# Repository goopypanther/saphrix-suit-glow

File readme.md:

#Daisy-chainable RGB LED boards, interfaced through clocked serial (shift register).#

Daisy chain slave, single address:

Daisy chain slave, dual address:

ISM 400mhz remote control:

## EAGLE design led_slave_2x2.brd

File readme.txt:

Daisy-chainable RGB LED boards, interfaced through clocked serial (shift register).

Daisy chain slave, single address:
(https://github.com/JeremyRuhland/saphrix-suit-glow/raw/master/led_slave_1x2.png)

Daisy chain slave, dual address:
(https://github.com/JeremyRuhland/saphrix-suit-glow/raw/master/led_slave_2x2.png)

ISM 400mhz remote control:
(https://raw.github.com/JeremyRuhland/saphrix-suit-glow/master/led_remote.png)

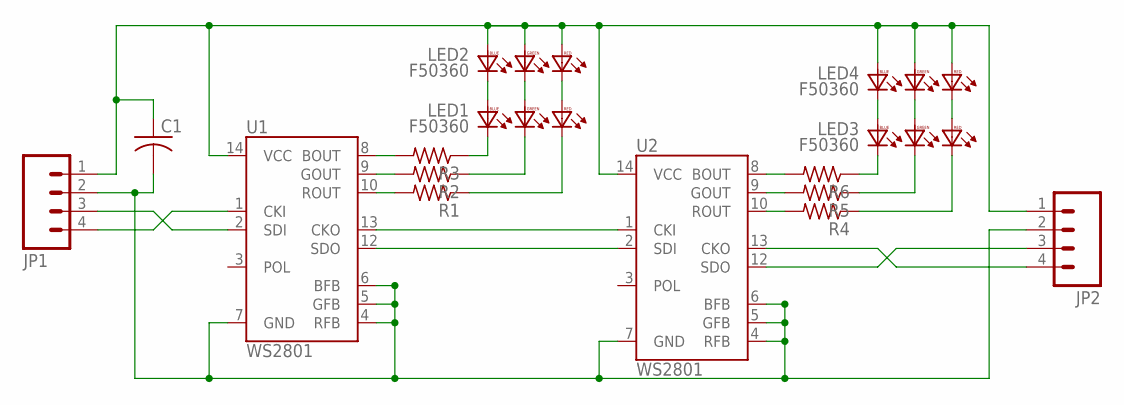
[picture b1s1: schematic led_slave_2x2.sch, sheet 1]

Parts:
C1: C-USC1206; C1206
JP1, JP2: M04LONGPADS; 1X04_LONGPADS
LED1, LED2, LED3, LED4: F50360
R1, R2, R3, R4, R5, R6: R-US_R1206; R1206
U1, U2: WS2801; SOP-14

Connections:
unnamed: JP1.3, U1.2 (SDI)
unnamed: JP1.4, U1.1 (CKI)
unnamed: U1.13 (CKO), U2.1 (CKI)
unnamed: U1.12 (SDO), U2.2 (SDI)
unnamed: R1.2, U1.10 (ROUT)
unnamed: R2.2, U1.9 (GOUT)
unnamed: R3.2, U1.8 (BOUT)
unnamed: LED3.BA, LED4.BC
unnamed: LED3.GA, LED4.GC
unnamed: LED3.RA, LED4.RC
unnamed: LED1.BC, R3.1
unnamed: LED1.GC, R2.1
unnamed: JP2.3, U2.12 (SDO)
unnamed: JP2.4, U2.13 (CKO)
unnamed: LED1.BA, LED2.BC
unnamed: LED1.GA, LED2.GC
unnamed: LED1.RA, LED2.RC
unnamed: LED3.BC, R6.1
unnamed: LED3.GC, R5.1
unnamed: LED3.RC, R4.1
unnamed: LED1.RC, R1.1
unnamed: R6.2, U2.8 (BOUT)
unnamed: R5.2, U2.9 (GOUT)
unnamed: R4.2, U2.10 (ROUT)
unnamed: C1.2, JP1.2, JP2.2, U1.4 (RFB), U1.5 (GFB), U1.6 (BFB), U1.7 (GND), U2.4 (RFB), U2.5 (GFB), U2.6 (BFB), U2.7 (GND)
unnamed: C1.1, JP1.1, JP2.1, LED2.BA, LED2.GA, LED2.RA, LED4.BA, LED4.GA, LED4.RA, U1.14 (VCC), U2.14 (VCC)

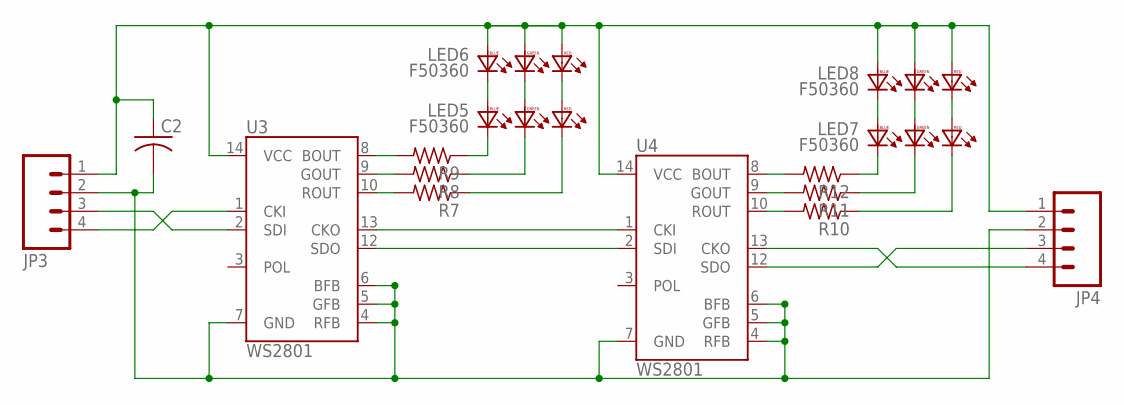
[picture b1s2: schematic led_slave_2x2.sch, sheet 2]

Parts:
C2: C-USC1206; C1206
JP3, JP4: M04LONGPADS; 1X04_LONGPADS
LED5, LED6, LED7, LED8: F50360
R7, R8, R9, R10, R11, R12: R-US_R1206; R1206
U3, U4: WS2801; SOP-14

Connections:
unnamed: U3.13 (CKO), U4.1 (CKI)
unnamed: U3.12 (SDO), U4.2 (SDI)
unnamed: LED5.BA, LED6.BC
unnamed: LED5.GA, LED6.GC
unnamed: LED5.RA, LED6.RC
unnamed: R7.2, U3.10 (ROUT)
unnamed: R8.2, U3.9 (GOUT)
unnamed: R9.2, U3.8 (BOUT)
unnamed: LED5.BC, R9.1
unnamed: LED5.GC, R8.1
unnamed: LED5.RC, R7.1
unnamed: LED7.BA, LED8.BC
unnamed: LED7.GA, LED8.GC
unnamed: LED7.RA, LED8.RC
unnamed: LED7.BC, R12.1
unnamed: LED7.GC, R11.1
unnamed: LED7.RC, R10.1
unnamed: R12.2, U4.8 (BOUT)
unnamed: R11.2, U4.9 (GOUT)
unnamed: R10.2, U4.10 (ROUT)
unnamed: C2.2, JP3.2, JP4.2, U3.4 (RFB), U3.5 (GFB), U3.6 (BFB), U3.7 (GND), U4.4 (RFB), U4.5 (GFB), U4.6 (BFB), U4.7 (GND)
unnamed: JP3.3, U3.2 (SDI)
unnamed: JP3.4, U3.1 (CKI)
unnamed: JP4.3, U4.12 (SDO)
unnamed: JP4.4, U4.13 (CKO)
unnamed: C2.1, JP3.1, JP4.1, LED6.BA, LED6.GA, LED6.RA, LED8.BA, LED8.GA, LED8.RA, U3.14 (VCC), U4.14 (VCC)

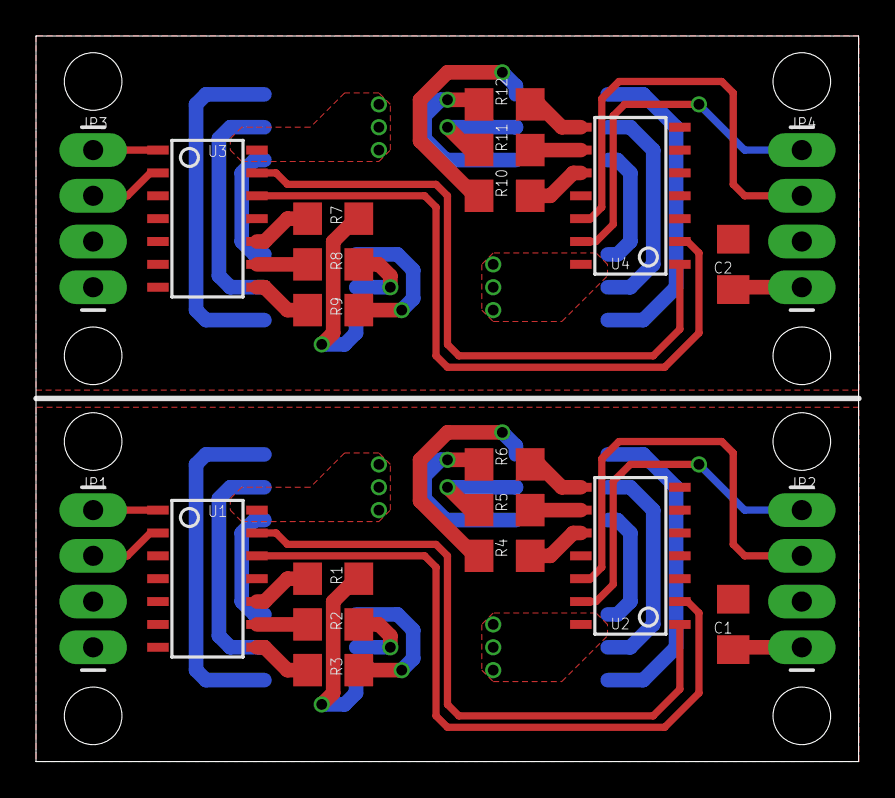
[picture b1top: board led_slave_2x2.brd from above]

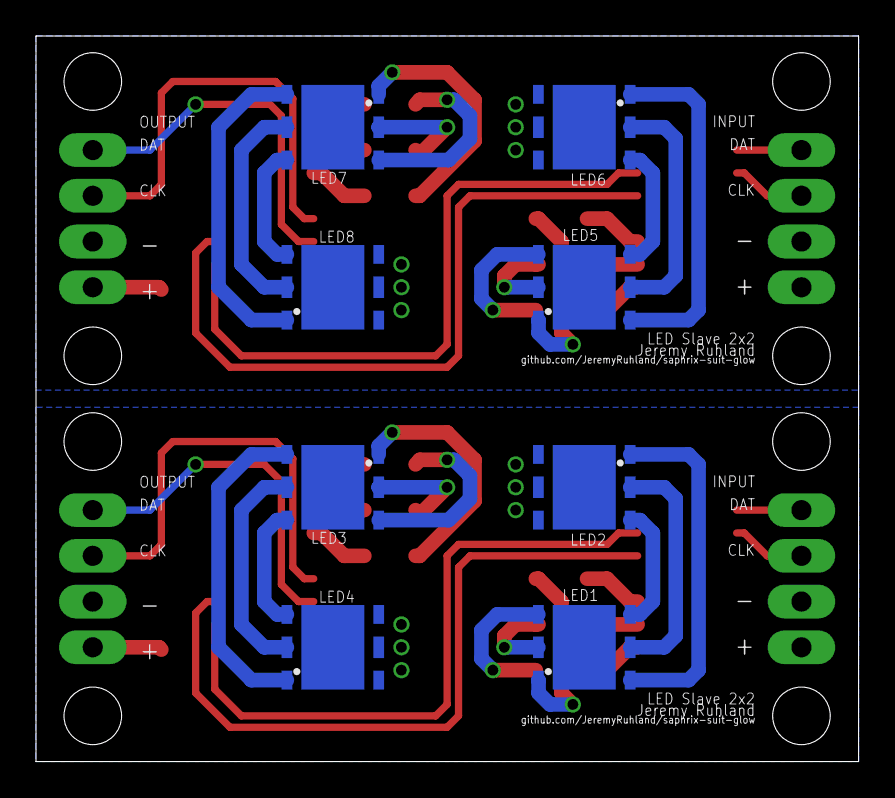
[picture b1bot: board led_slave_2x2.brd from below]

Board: 2 copper layers, 45.7 x 40.3 mm, 30 parts (8 on the bottom side), 52 nets.

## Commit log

2012-07-31 Fist commit, added two forms of slave boards and datasheet.
2012-07-31 fixed spacing and ground plain power concerns
2012-07-31 added readme
2012-07-31 trying to add images into readme
2012-08-06 Added more datasheet pdfs.
2012-08-06 Updated board design
2012-08-06 Created led_remote
2012-08-06 programmed led_remote
2012-08-06 started programming led_master
2012-08-20 added datasheets for additional components
2012-08-20 updated sch files
2012-08-20 added partial work on removable chest plate
2012-08-20 upadated readme with new image
2012-08-21 changed readme to markdown format
2012-08-21 deleted readme.txt
2012-08-21 formatting readme

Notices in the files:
parts and their libraries:
sparkfun: Licensing: CC v3.0 Share-Alike You are welcome to use this library for commercial purposes.
